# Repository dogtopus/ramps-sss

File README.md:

# RAMPS SSS

TMC2130 (SilentStepStick) SPI Adapter for RAMPS v1.4

## Features

- Dedicated 4-pin connector for each TMC2130 unit. Works with either .1" cable assemblies or individual jumper wires.
- Intuitive pinouts.
- Passthrough connectors for both Aux2 and Aux3 enable access to unused pins. Can co-exist with SPI SD card reader.

## BOM

J1, J2: **Angled** double row female .1" header.
J3: Straight double row male .1" header (can also use 5x 4-position colored single row headers for better pin differentiation)
J4, J5: Angled double row male .1" header.

## SS pin allocations

| SS | Axis | RAMPS Pin | 
| --- | --- | --- |
| 0 | X | D40 |
| 1 | Y | D42 |
| 2 | Z | D44 |
| 3 | E0 | D63/A9 |
| 4 | E1 | D64/A10 |

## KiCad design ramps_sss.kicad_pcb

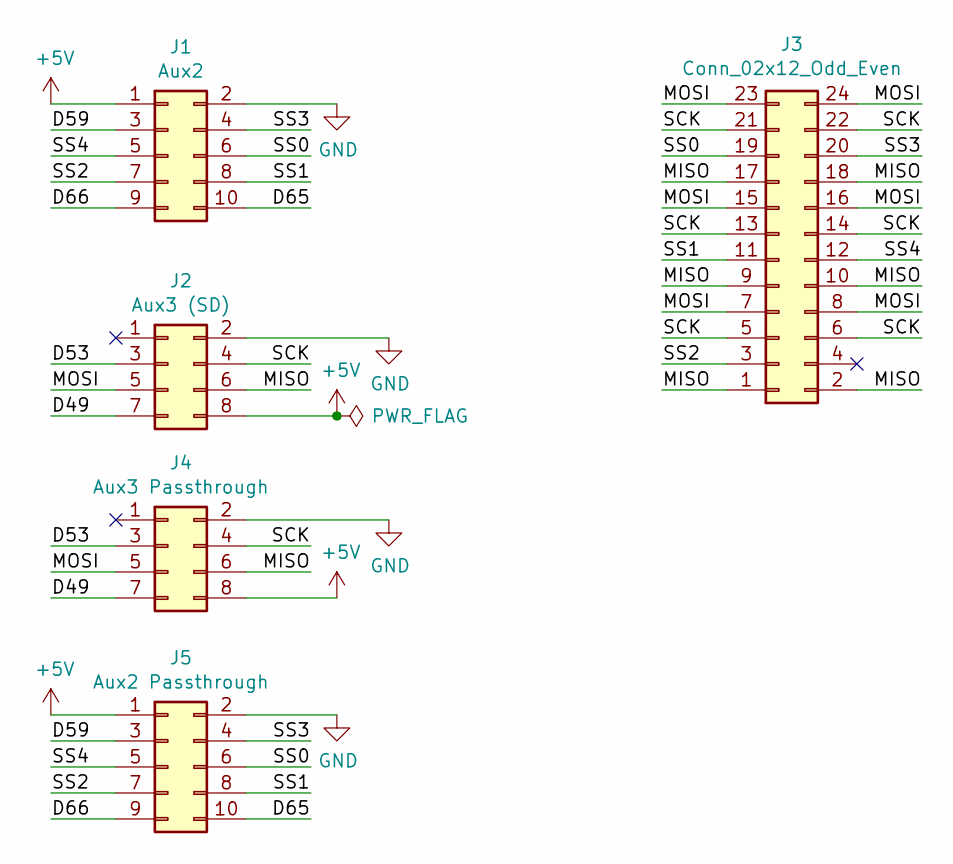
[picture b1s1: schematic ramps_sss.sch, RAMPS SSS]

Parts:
J1: Aux2; PinSocket_2x05_P2.54mm_Vertical
J2: Aux3 (SD); PinSocket_2x04_P2.54mm_Vertical
J3: Conn_02x12_Odd_Even; PinHeader_2x12_P2.54mm_Vertical
J4: Aux3 Passthrough; PinHeader_2x04_P2.54mm_Horizontal
J5: Aux2 Passthrough; PinHeader_2x05_P2.54mm_Horizontal

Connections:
+5V: J1.1, J2.8, J4.8, J5.1
/D49: J2.7, J4.7
/D53: J2.3, J4.3
/D59: J1.3, J5.3
/D65: J1.10, J5.10
/D66: J1.9, J5.9
/MISO: J2.6, J3.1, J3.2, J3.9, J3.10, J3.17, J3.18, J4.6
/MOSI: J2.5, J3.7, J3.8, J3.15, J3.16, J3.23, J3.24, J4.5
/SCK: J2.4, J3.5, J3.6, J3.13, J3.14, J3.21, J3.22, J4.4
/SS0: J1.6, J3.19, J5.6
/SS1: J1.8, J3.11, J5.8
/SS2: J1.7, J3.3, J5.7
/SS3: J1.4, J3.20, J5.4
/SS4: J1.5, J3.12, J5.5
GND: J1.2, J2.2, J4.2, J5.2

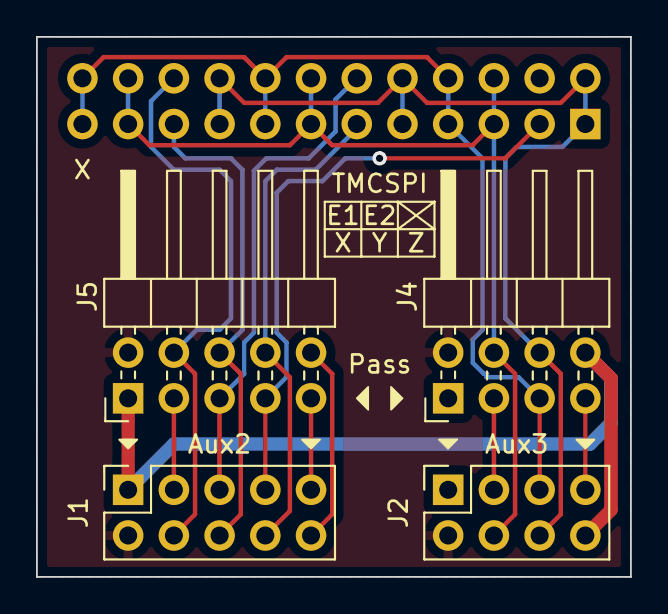
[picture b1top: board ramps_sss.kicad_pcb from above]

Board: 2 copper layers, 33.0 x 30.0 mm, 5 parts (1 on the bottom side), 15 nets.

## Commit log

2020-10-01 Add preview
